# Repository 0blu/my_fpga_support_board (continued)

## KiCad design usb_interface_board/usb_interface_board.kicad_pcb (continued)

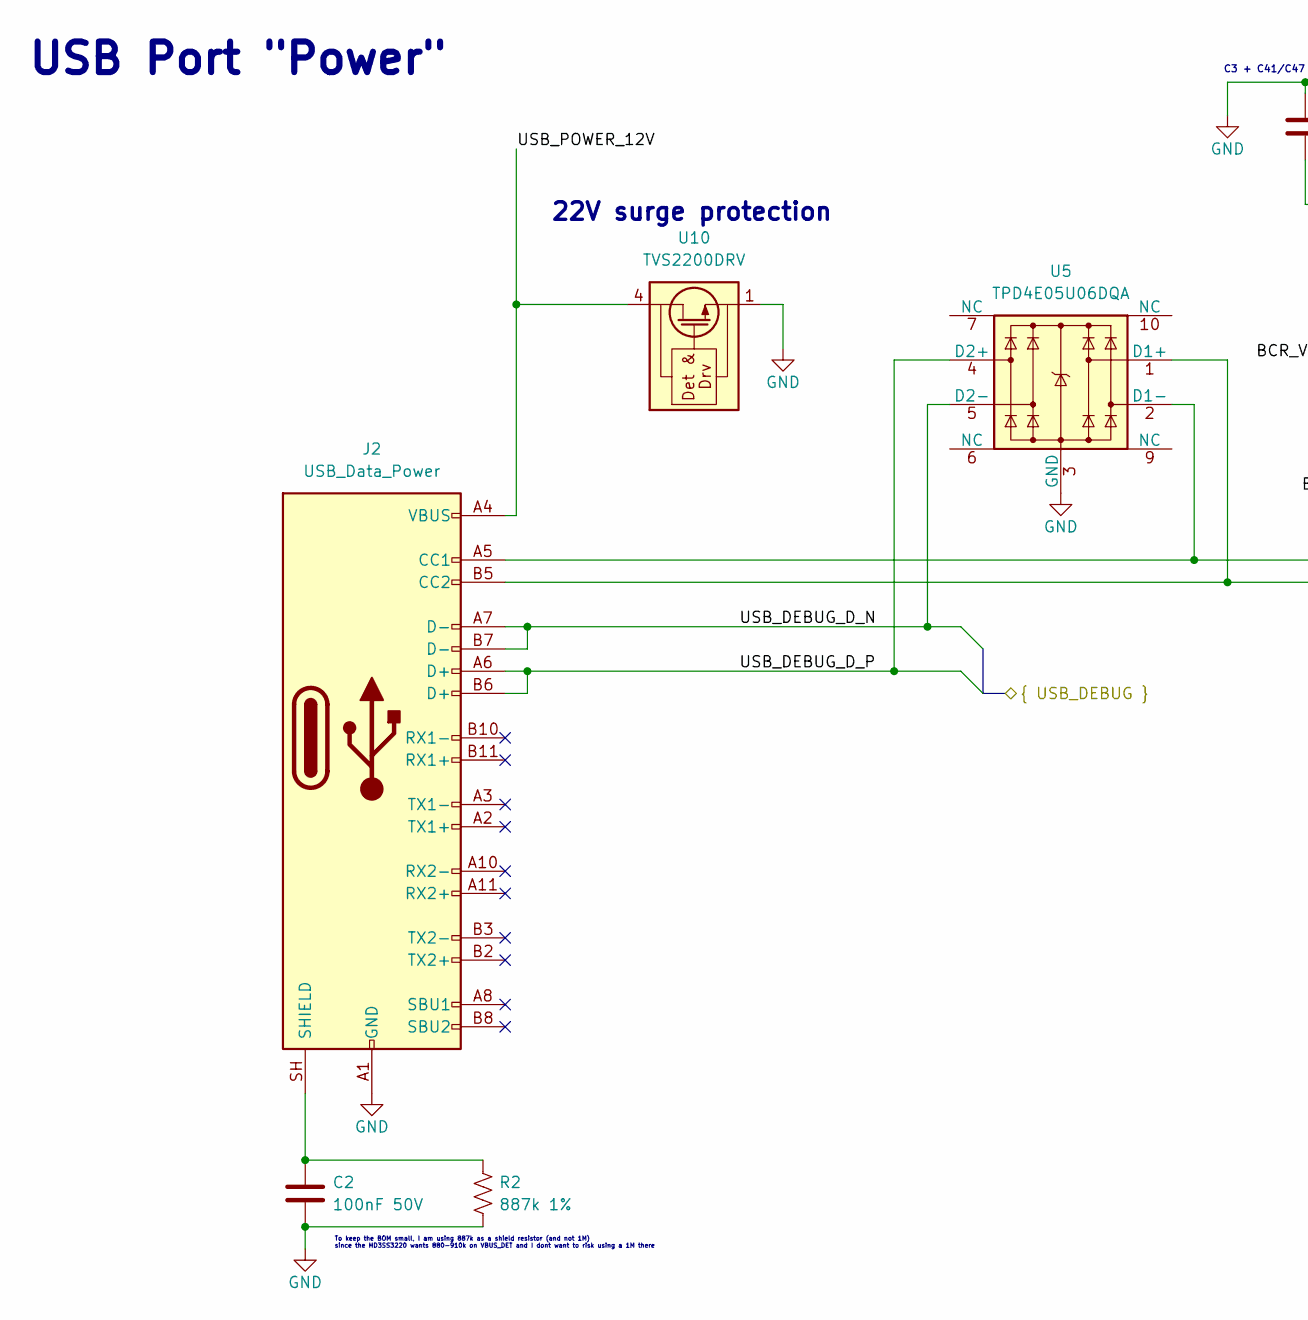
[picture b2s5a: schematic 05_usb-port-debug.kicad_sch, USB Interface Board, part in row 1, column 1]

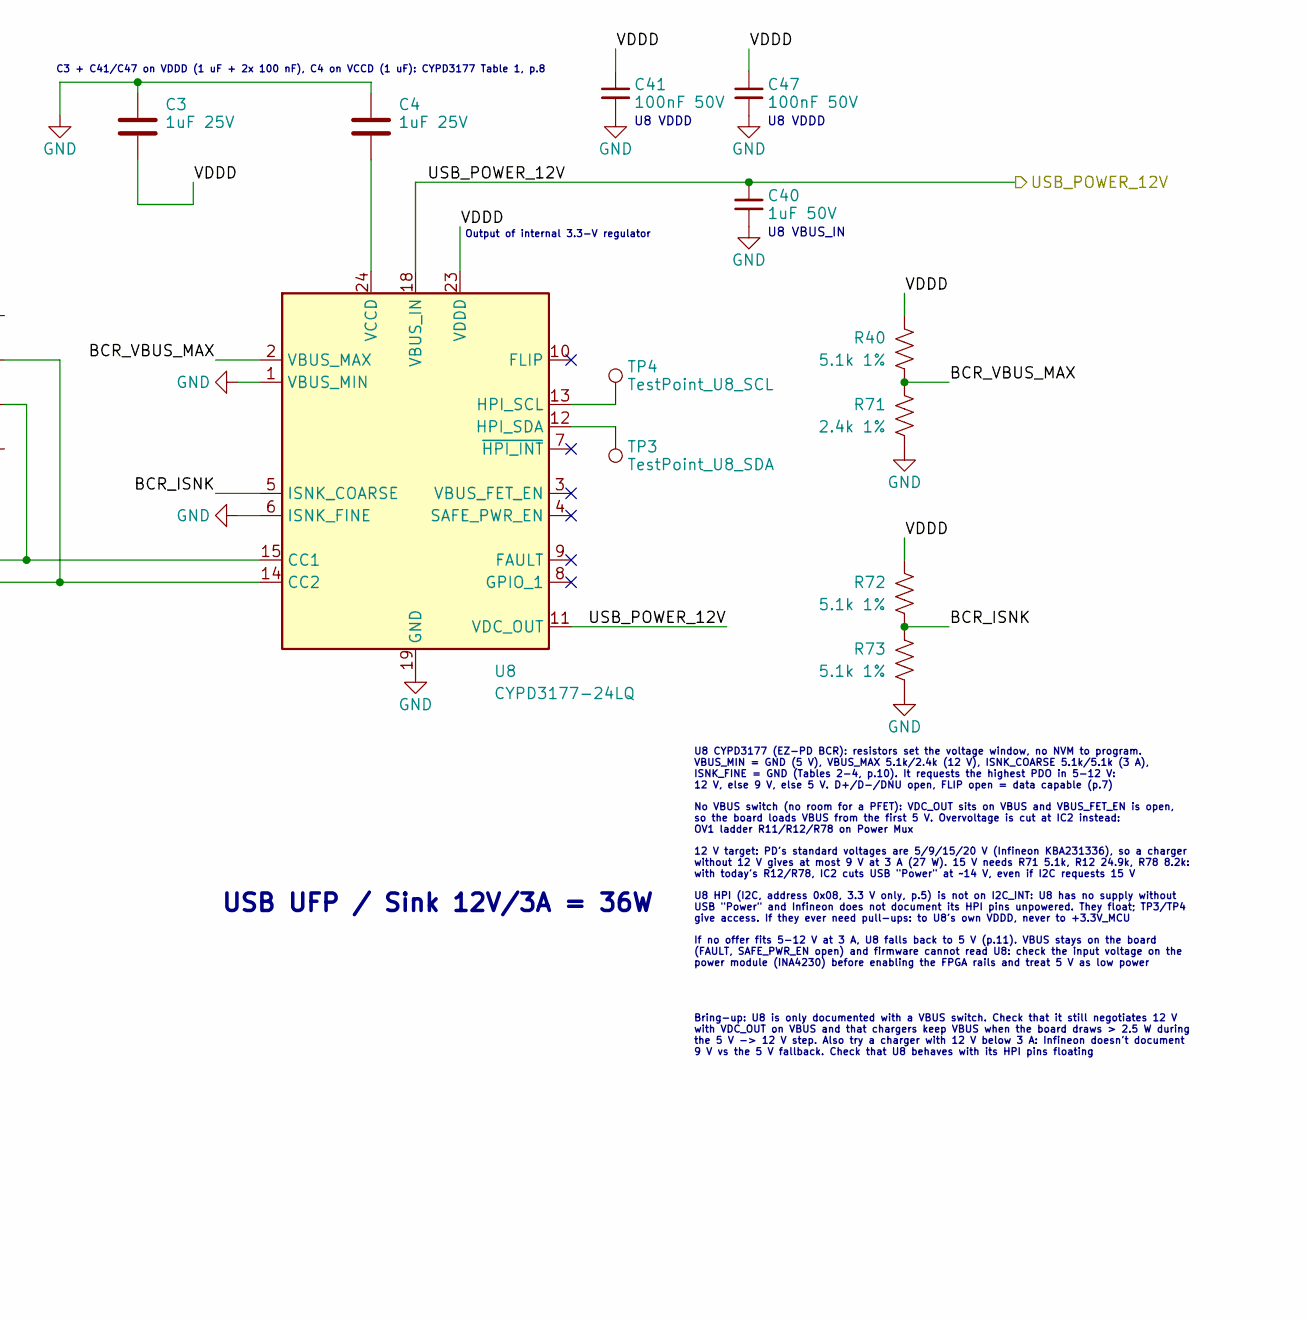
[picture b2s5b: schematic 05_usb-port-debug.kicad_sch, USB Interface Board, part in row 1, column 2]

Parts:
C2, C41, C47: 100nF 50V; C_0402_1005Metric; Manufacturer Part CL05B104KB54PNC; LCSC C307331
C3, C4: 1uF 25V; C_0402_1005Metric; Manufacturer Part CL05A105KA5NQNC; LCSC C52923
C40: 1uF 50V; C_0603_1608Metric; Manufacturer Part CL10A105KB8NNNC; LCSC C15849
J2: USB_Data_Power; USB_C_Receptacle_Molex_105450-0101; Manufacturer Part 105450-0101; LCSC C134092
R2: 887k 1%; R_0402_1005Metric; Manufacturer Part ERJ-2RKF8873X; LCSC C409935
R40, R72, R73: 5.1k 1%; R_0402_1005Metric; Manufacturer Part 0402WGF5101TCE; LCSC C25905
R71: 2.4k 1%; R_0402_1005Metric; Manufacturer Part RC0402FR-072K4L; LCSC C112296
TP3: TestPoint_U8_SDA; TestPoint_Pad_D1.0mm
TP4: TestPoint_U8_SCL; TestPoint_Pad_D1.0mm
U5: TPD4E05U06DQA; USON-10_2.5x1.0mm_P0.5mm; Manufacturer Part TPD4E05U06DQAR; LCSC C138714
U8: CYPD3177-24LQ; QFN-24-1EP_4x4mm_P0.5mm_EP2.75x2.75mm; Manufacturer Part CYPD3177-24LQXQT; LCSC C2952489
U10: TVS2200DRV; WSON-6-1EP_2x2mm_P0.65mm_EP1x1.6mm; Manufacturer Part TVS2200DRVR; LCSC C523793

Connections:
/EZ-USB 3.2 FX5/USB_DEBUG_D_N: J2.A7 (D-), J2.B7 (D-), U5.5 (D2-); also elsewhere on the board
/EZ-USB 3.2 FX5/USB_DEBUG_D_P: J2.A6 (D+), J2.B6 (D+), U5.4 (D2+); also elsewhere on the board
/USB Port "Power"/BCR_ISNK: R72.2, R73.1, U8.5 (ISNK_COARSE)
/USB Port "Power"/BCR_VBUS_MAX: R40.2, R71.1, U8.2 (VBUS_MAX)
/USB Port "Power"/USB_POWER_12V: C40.1, J2.A4 (VBUS), J2.A9 (VBUS), J2.B4 (VBUS), J2.B9 (VBUS), U8.11 (VDC_OUT), U8.18 (VBUS_IN), U10.4 (IN), U10.5 (IN), U10.6 (IN); also elsewhere on the board
/USB Port "Power"/VDDD: C3.2, C41.1, C47.1, R40.1, R72.1, U8.23 (VDDD)
GND: C2.2, C3.1, C4.1, C40.2, C41.2, C47.2, J2.A1 (GND), J2.A12 (GND), J2.B1 (GND), J2.B12 (GND), R2.2, R71.2, R73.2, U5.3 (GND), U5.8 (GND), U8.1 (VBUS_MIN), U8.6 (ISNK_FINE), U8.19 (GND), U8.22 (GND), U8.25 (GND), U10.1 (GND), U10.2 (GND), U10.3 (GND), U10.7 (GND); also elsewhere on the board
unnamed: J2.A5 (CC1), U5.2 (D1-), U8.15 (CC1)
unnamed: J2.B5 (CC2), U5.1 (D1+), U8.14 (CC2)
unnamed: C2.1, J2.SH (SHIELD), R2.1
unnamed: TP4.1 (1_1), U8.13 (HPI_SCL)
unnamed: TP3.1 (1_1), U8.12 (HPI_SDA)
unnamed: C4.2, U8.24 (VCCD)

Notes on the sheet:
U8 HPI (I2C, address 0x08, 3.3 V only, p.5) is not on I2C_INT: U8 has no supply without USB "Power" and Infineon does not document its HPI pins unpowered. They float; TP3/TP4 give access. If they ever need pull-ups: to U8's own VDDD, never to +3.3V_MCU
12 V target: PD's standard voltages are 5/9/15/20 V (Infineon KBA231336), so a charger without 12 V gives at most 9 V at 3 A (27 W). 15 V needs R71 5.1k, R12 24.9k, R78 8.2k: with today's R12/R78, IC2 cuts USB "Power" at ~14 V, even if I2C requests 15 V
Bring-up: U8 is only documented with a VBUS switch. Check that it still negotiates 12 V with VDC_OUT on VBUS and that chargers keep VBUS when the board draws > 2.5 W during the 5 V -> 12 V step. Also try a charger with 12 V below 3 A: Infineon doesn't document 9 V vs the 5 V fallback. Check that U8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
U8 VDDD
U8 VBUS_IN
To keep the BOM small, I am using 887k as a shield resistor (and not 1M) since the HD3SS3220 wants 880-910k on VBUS_DET and I dont want to risk using a 1M there
Output of internal 3.3-V regulator
USB Port "Power"
No VBUS switch (no room for a PFET): VDC_OUT sits on VBUS and VBUS_FET_EN is open, so the board loads VBUS from the first 5 V. Overvoltage is cut at IC2 instead: OV1 ladder R11/R12/R78 on Power Mux
U8 CYPD3177 (EZ-PD BCR): resistors set the voltage window, no NVM to program. VBUS_MIN = GND (5 V), VBUS_MAX 5.1k/2.4k (12 V), ISNK_COARSE 5.1k/5.1k (3 A), ISNK_FINE = GND (Tables 2-4, p.10). It requests the highest PDO in 5-12 V: 12 V, else 9 V, else 5 V. D+/D-/DNU open, FLIP open = data capable (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
22V surge protection
C3 + C41/C47 on VDDD (1 uF + 2x 100 nF), C4 on VCCD (1 uF): CYPD3177 Table 1, p.8
USB UFP / Sink 12V/3A = 36W
If no offer fits 5-12 V at 3 A, U8 falls back to 5 V (p.11). VBUS stays on the board (FAULT, SAFE_PWR_EN open) and firmware cannot read U8: check the input voltage on the power module (INA4230) before enabling the FPGA rails and treat 5 V as low power

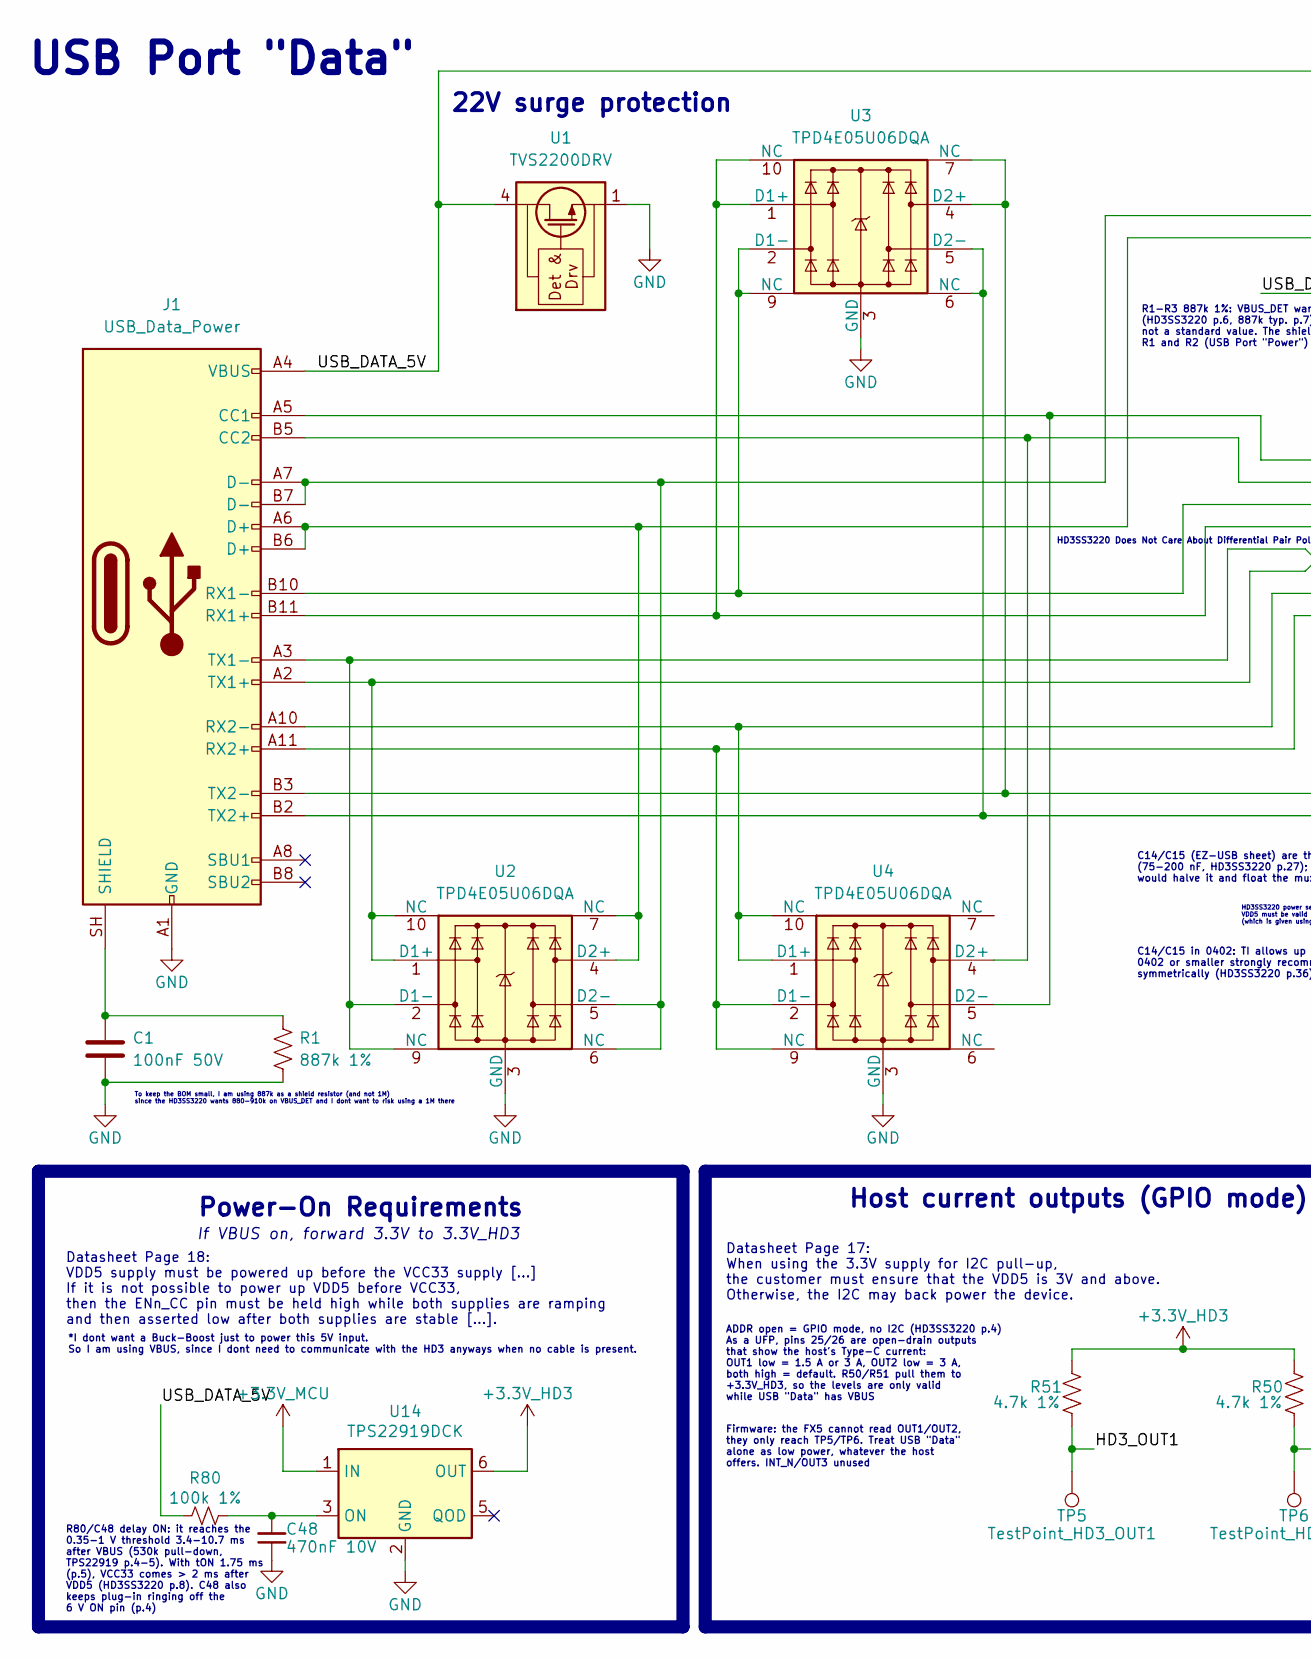
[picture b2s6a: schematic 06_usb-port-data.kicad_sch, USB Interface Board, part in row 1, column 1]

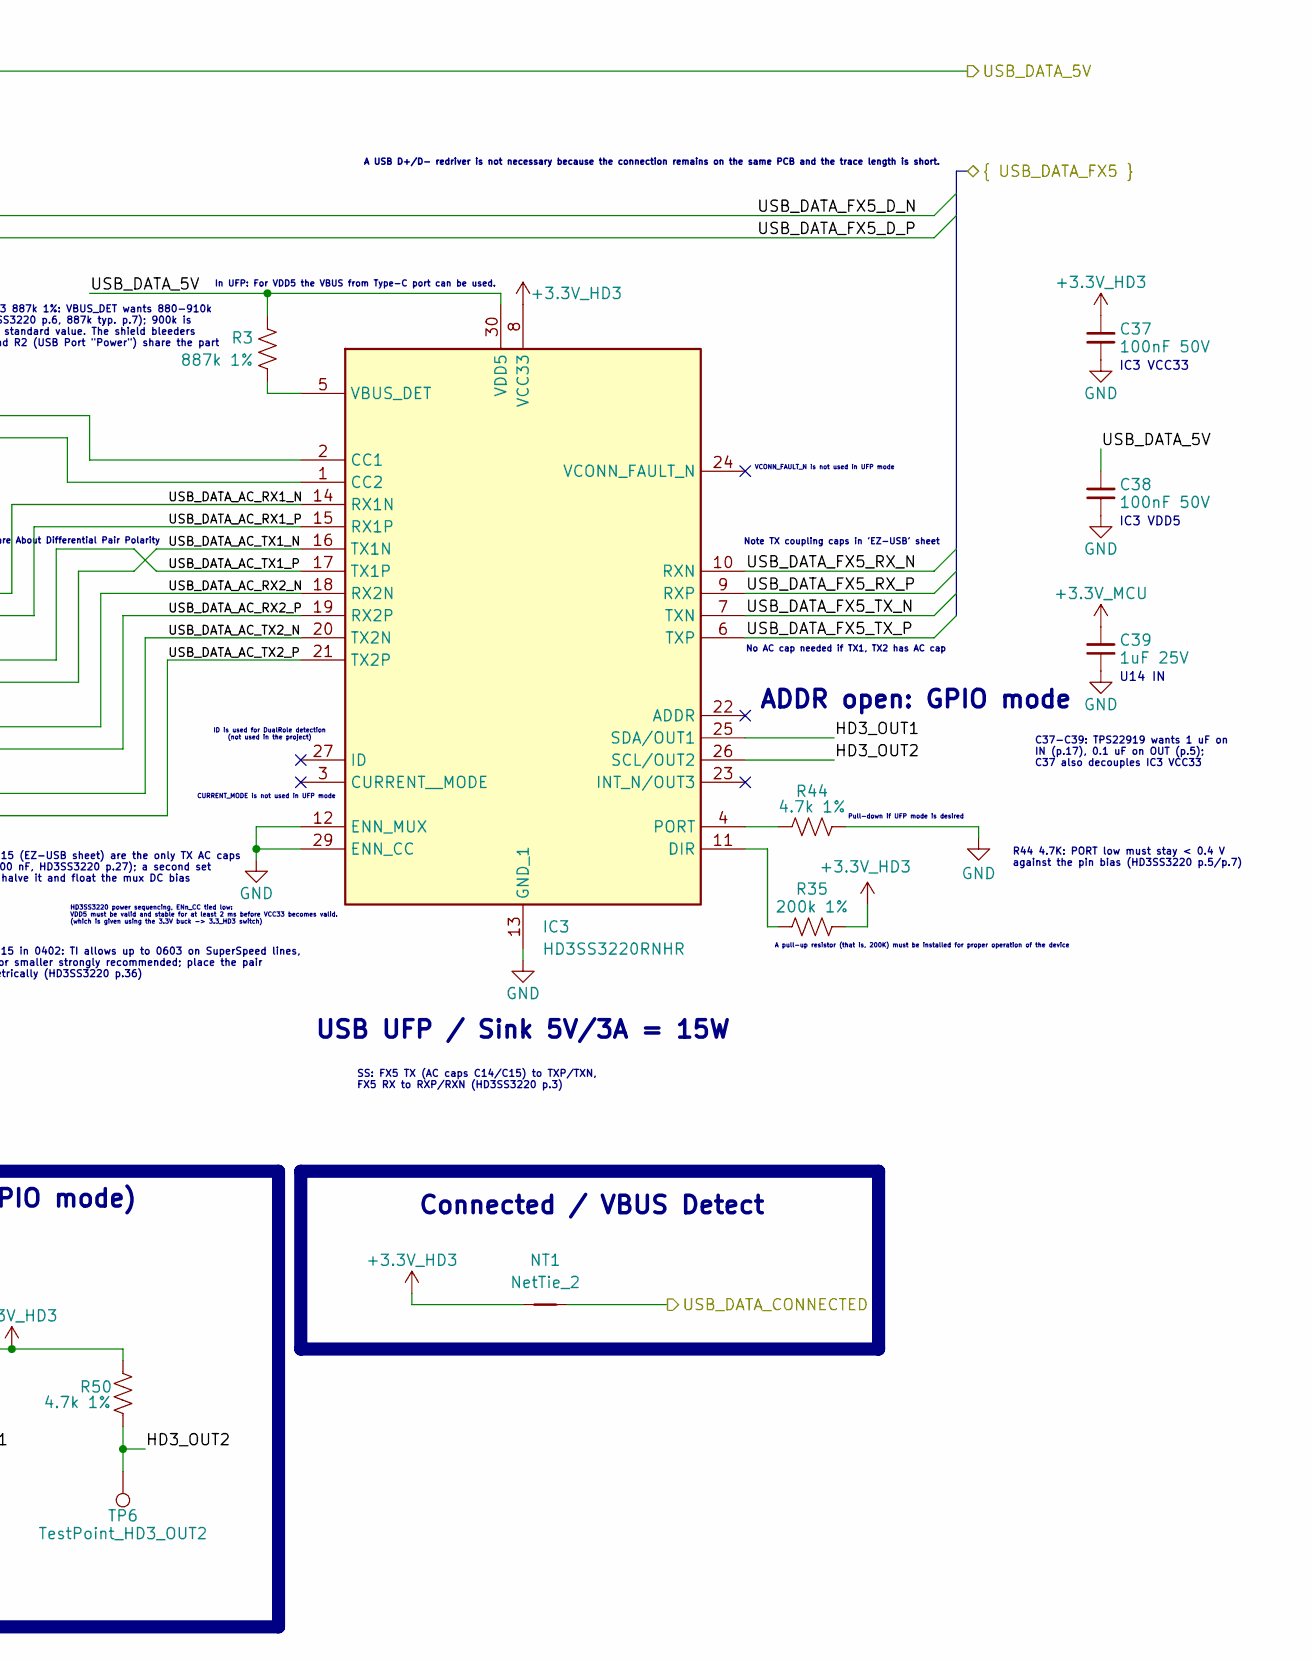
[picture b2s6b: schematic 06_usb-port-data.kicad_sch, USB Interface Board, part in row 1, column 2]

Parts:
C1, C37, C38: 100nF 50V; C_0402_1005Metric; Manufacturer Part CL05B104KB54PNC; LCSC C307331
C39: 1uF 25V; C_0402_1005Metric; Manufacturer Part CL05A105KA5NQNC; LCSC C52923
C48: 470nF 10V; C_0402_1005Metric; Manufacturer Part CL05A474KP5NNNC; LCSC C47339
IC3: HD3SS3220RNHR; QFN40P250X450X80-31N-D; Mouser Part Number 595-HD3SS3220RNHR
J1: USB_Data_Power; USB_C_Receptacle_Molex_105450-0101; Manufacturer Part 105450-0101; LCSC C134092
NT1: NetTie_2; NetTie-2_SMD_Pad0.15mm
R1, R3: 887k 1%; R_0402_1005Metric; Manufacturer Part ERJ-2RKF8873X; LCSC C409935
R35: 200k 1%; R_0402_1005Metric; Manufacturer Part 0402WGF2003TCE; LCSC C25764
R44, R50, R51: 4.7k 1%; R_0402_1005Metric; Manufacturer Part 0402WGF4701TCE; LCSC C25900
R80: 100k 1%; R_0402_1005Metric; Manufacturer Part 0402WGF1003TCE; LCSC C25741
TP5: TestPoint_HD3_OUT1; TestPoint_Pad_D1.0mm
TP6: TestPoint_HD3_OUT2; TestPoint_Pad_D1.0mm
U1: TVS2200DRV; WSON-6-1EP_2x2mm_P0.65mm_EP1x1.6mm; Manufacturer Part TVS2200DRVR; LCSC C523793
U2, U3, U4: TPD4E05U06DQA; USON-10_2.5x1.0mm_P0.5mm; Manufacturer Part TPD4E05U06DQAR; LCSC C138714
U14: TPS22919DCK; SOT-363_SC-70-6; Manufacturer Part TPS22919DCKR; LCSC C2149796

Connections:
+3.3V_HD3: C37.1, IC3.8 (VCC33), NT1.1, R35.2, R50.1, R51.1, U14.6 (OUT)
+3.3V_MCU: C39.1, U14.1 (IN); also elsewhere on the board
/EZ-USB 3.2 FX5/USB_DATA_5V: C38.1, IC3.30 (VDD5), J1.A4 (VBUS), J1.A9 (VBUS), J1.B4 (VBUS), J1.B9 (VBUS), R3.2, R80.1, U1.4 (IN), U1.5 (IN), U1.6 (IN); also elsewhere on the board
/EZ-USB 3.2 FX5/USB_DATA_CONNECTED: NT1.2; also elsewhere on the board
/EZ-USB 3.2 FX5/USB_DATA_FX5_D_N: J1.A7 (D-), J1.B7 (D-), U2.5 (D2-), U2.6 (NC); also elsewhere on the board
/EZ-USB 3.2 FX5/USB_DATA_FX5_D_P: J1.A6 (D+), J1.B6 (D+), U2.4 (D2+), U2.7 (NC); also elsewhere on the board
/EZ-USB 3.2 FX5/USB_DATA_FX5_RX_N: IC3.10 (RXN); also elsewhere on the board
/EZ-USB 3.2 FX5/USB_DATA_FX5_RX_P: IC3.9 (RXP); also elsewhere on the board
/EZ-USB 3.2 FX5/USB_DATA_FX5_TX_N: IC3.7 (TXN); also elsewhere on the board
/EZ-USB 3.2 FX5/USB_DATA_FX5_TX_P: IC3.6 (TXP); also elsewhere on the board
/USB Port "Data"/HD3_OUT1: IC3.25 (SDA/OUT1), R51.2, TP5.1 (1_1)
/USB Port "Data"/HD3_OUT2: IC3.26 (SCL/OUT2), R50.2, TP6.1 (1_1)
/USB Port "Data"/USB_DATA_AC_RX1_N: IC3.14 (RX1N), J1.B10 (RX1-), U3.2 (D1-), U3.9 (NC)
/USB Port "Data"/USB_DATA_AC_RX1_P: IC3.15 (RX1P), J1.B11 (RX1+), U3.1 (D1+), U3.10 (NC)
/USB Port "Data"/USB_DATA_AC_RX2_N: IC3.18 (RX2N), J1.A10 (RX2-), U4.1 (D1+), U4.10 (NC)
/USB Port "Data"/USB_DATA_AC_RX2_P: IC3.19 (RX2P), J1.A11 (RX2+), U4.2 (D1-), U4.9 (NC)
/USB Port "Data"/USB_DATA_AC_TX1_N: IC3.16 (TX1N), J1.A2 (TX1+), U2.1 (D1+), U2.10 (NC)
/USB Port "Data"/USB_DATA_AC_TX1_P: IC3.17 (TX1P), J1.A3 (TX1-), U2.2 (D1-), U2.9 (NC)
/USB Port "Data"/USB_DATA_AC_TX2_N: IC3.20 (TX2N), J1.B3 (TX2-), U3.4 (D2+), U3.7 (NC)
/USB Port "Data"/USB_DATA_AC_TX2_P: IC3.21 (TX2P), J1.B2 (TX2+), U3.5 (D2-), U3.6 (NC)
GND: C1.2, C37.2, C38.2, C39.2, C48.2, IC3.12 (ENN_MUX), IC3.13 (GND_1), IC3.28 (GND_2), IC3.29 (ENN_CC), IC3.31 (EP), J1.A1 (GND), J1.A12 (GND), J1.B1 (GND), J1.B12 (GND), R1.2, R44.2, U1.1 (GND), U1.2 (GND), U1.3 (GND), U1.7 (GND), U2.3 (GND), U2.8 (GND), U3.3 (GND), U3.8 (GND), U4.3 (GND), U4.8 (GND), U14.2 (GND); also elsewhere on the board
unnamed: IC3.2 (CC1), J1.A5 (CC1), U4.5 (D2-)
unnamed: IC3.1 (CC2), J1.B5 (CC2), U4.4 (D2+)
unnamed: IC3.11 (DIR), R35.1
unnamed: IC3.4 (PORT), R44.1
unnamed: IC3.5 (VBUS_DET), R3.1
unnamed: C1.1, J1.SH (SHIELD), R1.1
unnamed: C48.1, R80.2, U14.3 (ON)

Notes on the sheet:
CURRENT_MODE is not used in UFP mode
Connected / VBUS Detect
R1-R3 887k 1%: VBUS_DET wants 880-910k (HD3SS3220 p.6, 887k typ. p.7); 900k is not a standard value. The shield bleeders R1 and R2 (USB Port "Power") share the part
ID is used for DualRole detection (not used in the project)
Power-On Requirements
Note TX coupling caps in 'EZ-USB' sheet
A pull-up resistor (that is, 200K) must be installed for proper operation of the device
USB Port "Data"
HD3SS3220 Does Not Care About Differential Pair Polarity
USB UFP / Sink 5V/3A = 15W
A USB D+/D− redriver is not necessary because the connection remains on the same PCB and the trace length is short.
Firmware: the FX5 cannot read OUT1/OUT2, they only reach TP5/TP6. Treat USB "Data" alone as low power, whatever the host offers. INT_N/OUT3 unused
HD3SS3220 power sequencing, ENn_CC tied low: VDD5 must be valid and stable for at least 2 ms before VCC33 becomes valid. (which is given using the 3.3V buck -> 3.3_HD3 switch)
R80/C48 delay ON: it reaches the 0.35-1 V threshold 3.4-10.7 ms after VBUS (530k pull-down, TPS22919 p.4-5). With tON 1.75 ms (p.5), VCC33 comes > 2 ms after VDD5 (HD3SS3220 p.8). C48 also keeps plug-in ringing off the 6 V ON pin (p.4)
If VBUS on, forward 3.3V to 3.3V_HD3
VCONN_FAULT_N is not used in UFP mode
Datasheet Page 17: When using the 3.3V supply for I2C pull-up, the customer must ensure that the VDD5 is 3V and above. Otherwise, the I2C may back power the device.
*I dont want a Buck-Boost just to power this 5V input. So I am using VBUS, since I dont need to communicate with the HD3 anyways when no cable is present.
SS: FX5 TX (AC caps C14/C15) to TXP/TXN, FX5 RX to RXP/RXN (HD3SS3220 p.3)
R44 4.7K: PORT low must stay < 0.4 V against the pin bias (HD3SS3220 p.5/p.7)
C14/C15 (EZ-USB sheet) are the only TX AC caps (75-200 nF, HD3SS3220 p.27); a second set would halve it and float the mux DC bias
IC3 VDD5
No AC cap needed if TX1, TX2 has AC cap
IC3 VCC33
Datasheet Page 18: VDD5 supply must be powered up before the VCC33 supply [...] If it is not possible to power up VDD5 before VCC33, then the ENn_CC pin must be held high while both supplies are ramping and then asserted low after both supplies are stable [...].
Host current outputs (GPIO mode)
U14 IN
C37-C39: TPS22919 wants 1 uF on IN (p.17), 0.1 uF on OUT (p.5); C37 also decouples IC3 VCC33
In UFP: For VDD5 the VBUS from Type-C port can be used.
C14/C15 in 0402: TI allows up to 0603 on SuperSpeed lines, 0402 or smaller strongly recommended; place the pair symmetrically (HD3SS3220 p.36)
To keep the BOM small, I am using 887k as a shield resistor (and not 1M) since the HD3SS3220 wants 880-910k on VBUS_DET and I dont want to risk using a 1M there
22V surge protection
ADDR open: GPIO mode
Pull-down if UFP mode is desired
ADDR open = GPIO mode, no I2C (HD3SS3220 p.4) As a UFP, pins 25/26 are open-drain outputs that show the host's Type-C current: OUT1 low = 1.5 A or 3 A, OUT2 low = 3 A, both high = default. R50/R51 pull them to +3.3V_HD3, so the levels are only valid while USB "Data" has VBUS

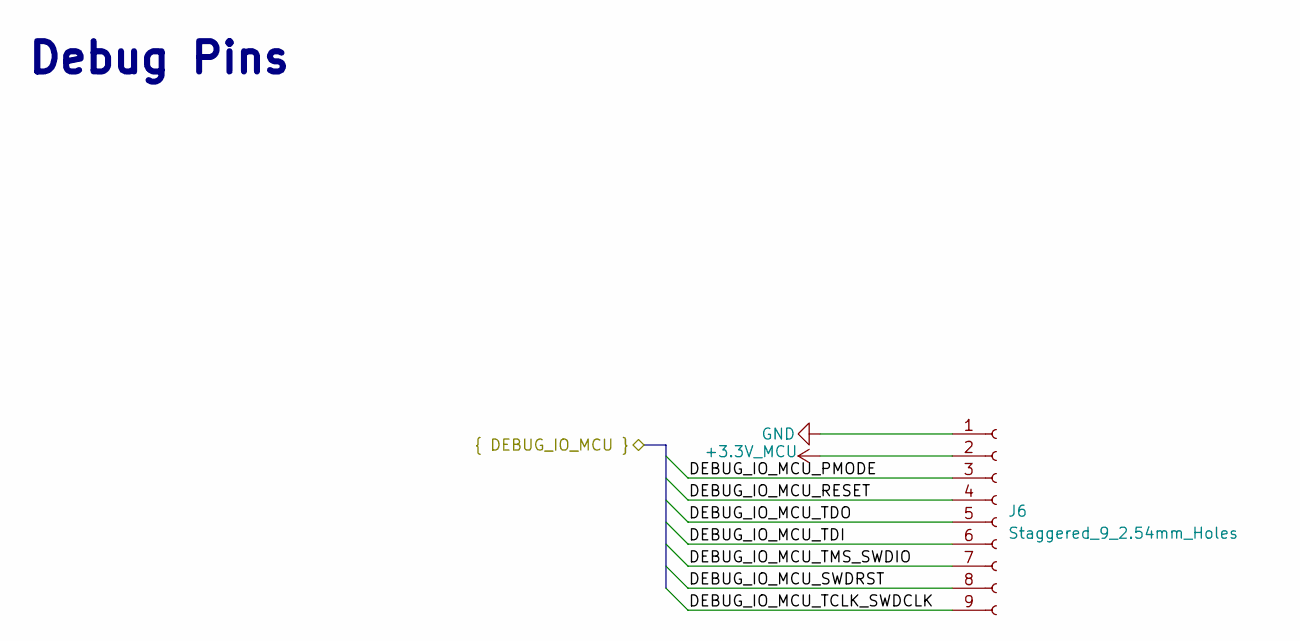
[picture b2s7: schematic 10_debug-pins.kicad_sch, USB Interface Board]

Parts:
J6: Staggered_9_2.54mm_Holes; 09_Staggered_GPIO_holes

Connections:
+3.3V_MCU: J6.2; also elsewhere on the board
/Debug Pins/DEBUG_IO_MCU_PMODE: J6.3; also elsewhere on the board
/Debug Pins/DEBUG_IO_MCU_RESET: J6.4; also elsewhere on the board
/Debug Pins/DEBUG_IO_MCU_SWDRST: J6.8; also elsewhere on the board
/Debug Pins/DEBUG_IO_MCU_TCLK_SWDCLK: J6.9; also elsewhere on the board
/Debug Pins/DEBUG_IO_MCU_TDI: J6.6; also elsewhere on the board
/Debug Pins/DEBUG_IO_MCU_TDO: J6.5; also elsewhere on the board
/Debug Pins/DEBUG_IO_MCU_TMS_SWDIO: J6.7; also elsewhere on the board
GND: J6.1; also elsewhere on the board

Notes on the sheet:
Debug Pins

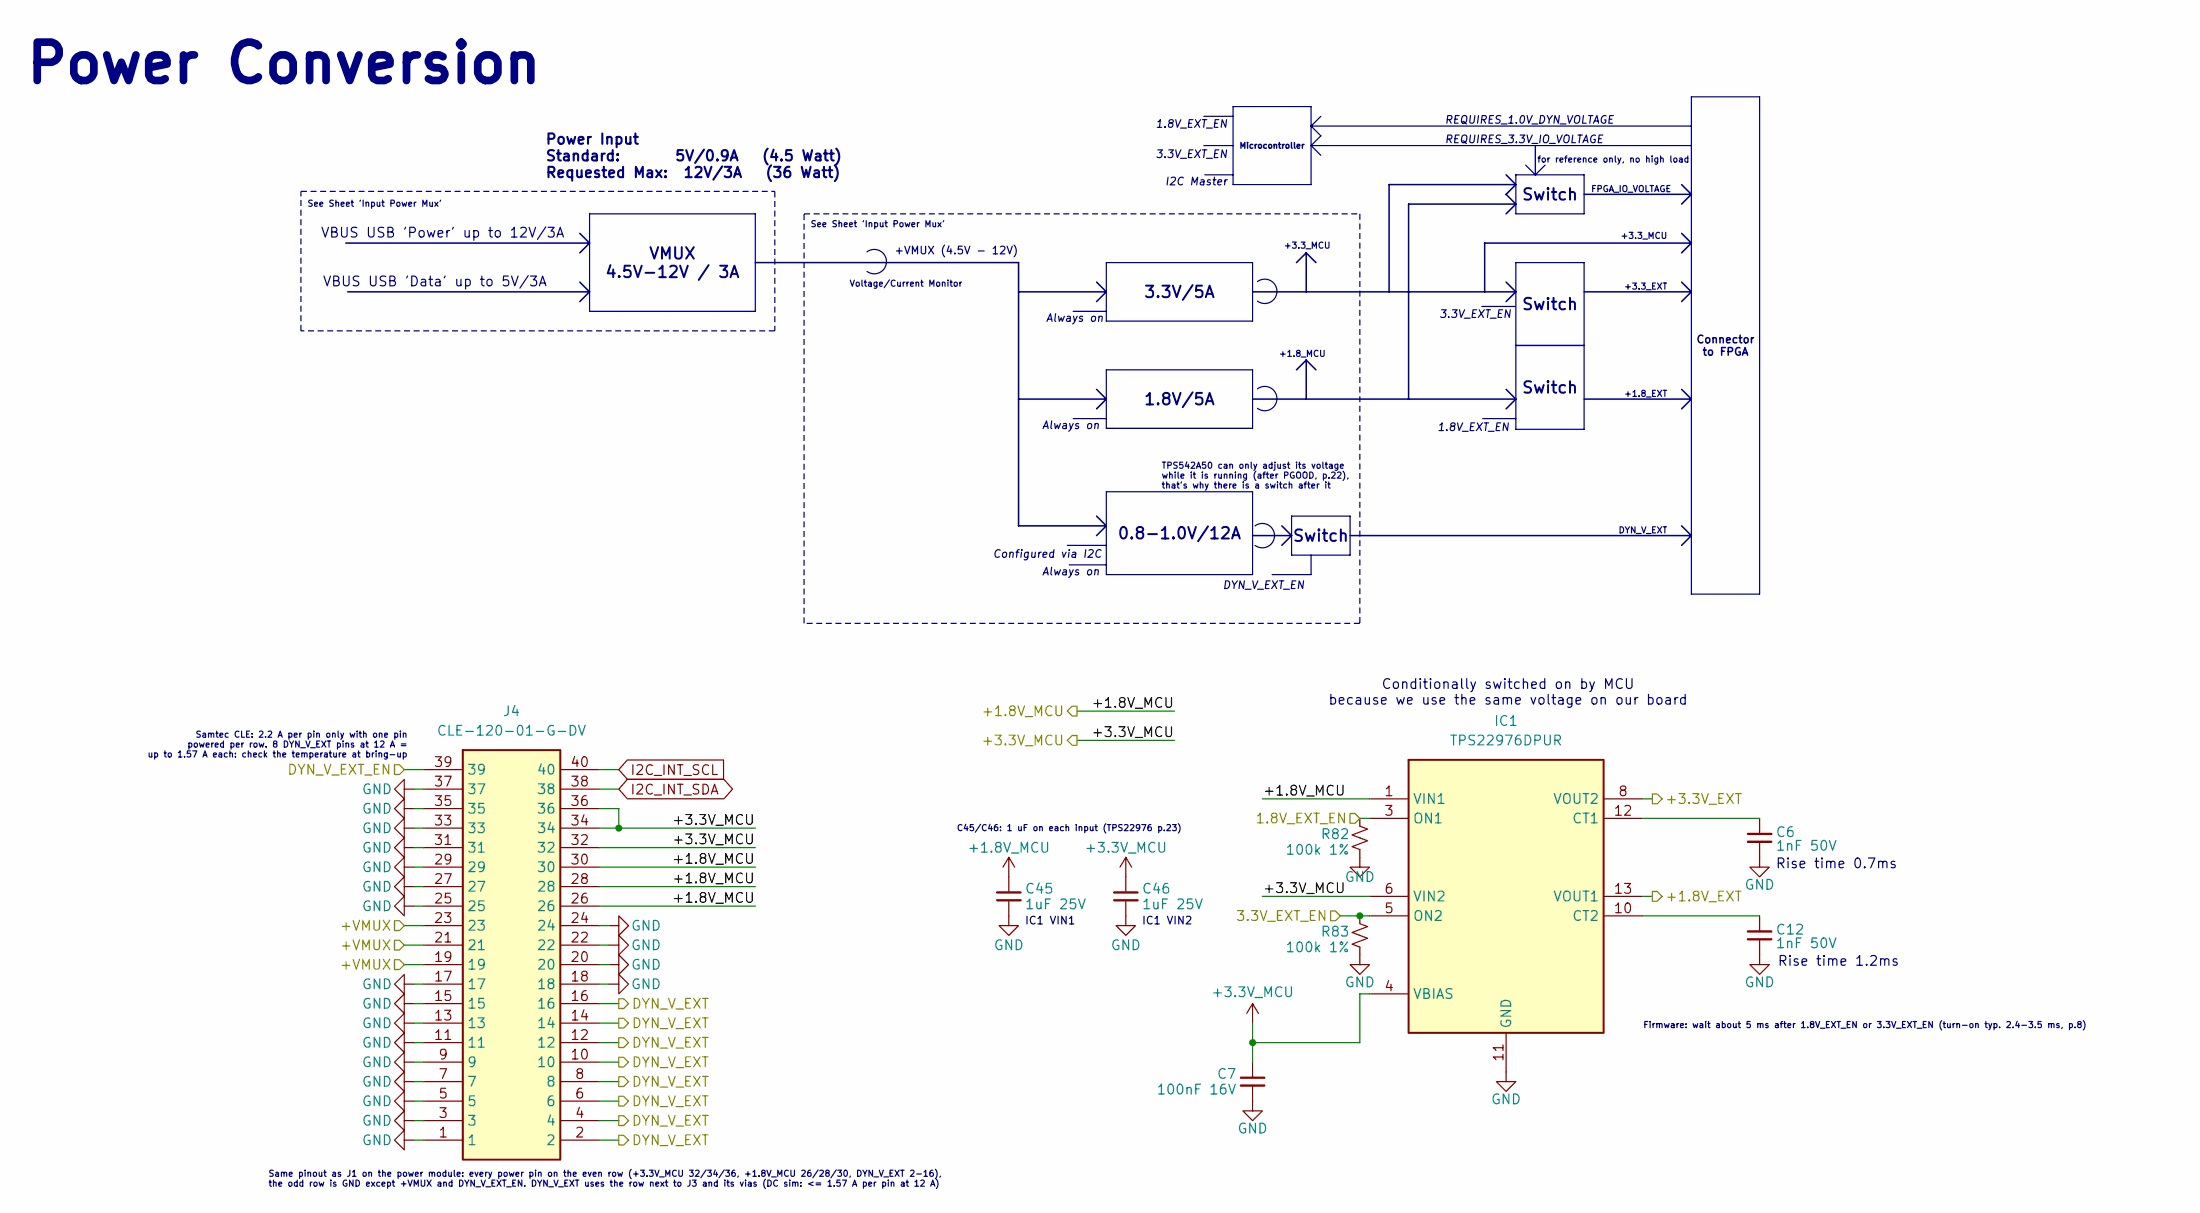
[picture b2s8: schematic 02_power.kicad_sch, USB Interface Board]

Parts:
C6, C12: 1nF 50V; C_0402_1005Metric; Manufacturer Part 0402B102K500NT; LCSC C1523
C7: 100nF 16V; C_0201_0603Metric; Manufacturer Part CL03A104KO3NNNC; LCSC C307380
C45, C46: 1uF 25V; C_0402_1005Metric; Manufacturer Part CL05A105KA5NQNC; LCSC C52923
IC1: TPS22976DPUR; TPS22976ADPUR; Mouser Part Number 595-TPS22976DPUR
J4: CLE-120-01-G-DV; Manufacturer Part CLE-120-01-G-DV-K-TR; LCSC C6484368
R82, R83: 100k 1%; R_0402_1005Metric; Manufacturer Part 0402WGF1003TCE; LCSC C25741

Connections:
+1.8V_MCU: C45.1, IC1.1 (VIN1), IC1.2 (VIN1_2), J4.26, J4.28, J4.30; also elsewhere on the board
+3.3V_MCU: C7.1, C46.1, IC1.4 (VBIAS), IC1.6 (VIN2), IC1.7 (VIN2_2), J4.32, J4.34, J4.36; also elsewhere on the board
/EZ-USB 3.2 FX5/1.8V_EXT_EN: IC1.3 (ON1), R82.1; also elsewhere on the board
/EZ-USB 3.2 FX5/3.3V_EXT_EN: IC1.5 (ON2), R83.1; also elsewhere on the board
/EZ-USB 3.2 FX5/DYN_V_EXT_EN: J4.39; also elsewhere on the board
/FPGA Board Connector/+1.8V_EXT: IC1.13 (VOUT1), IC1.14 (VOUT1_2); also elsewhere on the board
/FPGA Board Connector/+3.3V_EXT: IC1.8 (VOUT2), IC1.9 (VOUT2_2); also elsewhere on the board
/FPGA Board Connector/DYN_V_EXT: J4.2, J4.4, J4.6, J4.8, J4.10, J4.12, J4.14, J4.16; also elsewhere on the board
/Power Board Connector/+VMUX: J4.19, J4.21, J4.23; also elsewhere on the board
GND: C6.2, C7.2, C12.2, C45.2, C46.2, IC1.11 (GND), IC1.15 (GND_2), J4.1, J4.3, J4.5, J4.7, J4.9, J4.11, J4.13, J4.15, J4.17, J4.18, J4.20, J4.22, J4.24, J4.25, J4.27, J4.29, J4.31, J4.33, J4.35, J4.37, R82.2, R83.2; also elsewhere on the board
I2C_INT_SCL: J4.40; also elsewhere on the board
I2C_INT_SDA: J4.38; also elsewhere on the board
unnamed: C6.1, IC1.12 (CT1)
unnamed: C12.1, IC1.10 (CT2)

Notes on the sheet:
TPS542A50 can only adjust its voltage while it is running (after PGOOD, p.22), that's why there is a switch after it
+1.8_EXT
See Sheet 'Input Power Mux'
+3.3_MCU
Configured via I2C
DYN_V_EXT_EN
for reference only, no high load
REQUIRES_3.3V_IO_VOLTAGE
+3.3_EXT
Same pinout as J1 on the power module: every power pin on the even row (+3.3V_MCU 32/34/36, +1.8V_MCU 26/28/30, DYN_V_EXT 2-16), the odd row is GND except +VMUX and DYN_V_EXT_EN. DYN_V_EXT uses the row next to J3 and its vias (DC sim: <= 1.57 A per pin at 12 A)
IC1 VIN2
FPGA_IO_VOLTAGE
VBUS USB 'Data' up to 5V/3A
1.8V_EXT_EN
Always on
IC1 VIN1
Samtec CLE: 2.2 A per pin only with one pin powered per row. 8 DYN_V_EXT pins at 12 A = up to 1.57 A each: check the temperature at bring-up
Firmware: wait about 5 ms after 1.8V_EXT_EN or 3.3V_EXT_EN (turn-on typ. 2.4-3.5 ms, p.8)
Conditionally switched on by MCU because we use the same voltage on our board
Voltage/Current Monitor
VBUS USB 'Power' up to 12V/3A
+1.8_MCU
REQUIRES_1.0V_DYN_VOLTAGE
3.3V_EXT_EN
Rise time 1.2ms
Power Input Standard: 5V/0.9A (4.5 Watt) Requested Max: 12V/3A (36 Watt)
+VMUX (4.5V - 12V)
I2C Master
C45/C46: 1 uF on each input (TPS22976 p.23)
Power Conversion
DYN_V_EXT
Rise time 0.7ms
Switch
Connector to FPGA
0.8-1.0V/12A
1.8V/5A
VMUX 4.5V-12V / 3A
Microcontroller
3.3V/5A

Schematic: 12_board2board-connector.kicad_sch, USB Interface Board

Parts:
J3: QSH-030-01-L-D; QSH03001LDK; Manufacturer Part QSH-030-01-L-D-K-TR; LCSC C3653140

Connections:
+3.3V_MCU: J3.53; also elsewhere on the board
/100MHz Oscillator/CLK_100MHZ: J3.31; also elsewhere on the board
/EZ-USB 3.2 FX5/FIFO_A0: J3.48; also elsewhere on the board
/EZ-USB 3.2 FX5/FIFO_A1: J3.6; also elsewhere on the board
/EZ-USB 3.2 FX5/FIFO_CLK: J3.44; also elsewhere on the board
/EZ-USB 3.2 FX5/FIFO_D0: J3.2; also elsewhere on the board
/EZ-USB 3.2 FX5/FIFO_D1: J3.8; also elsewhere on the board
/EZ-USB 3.2 FX5/FIFO_D2: J3.16; also elsewhere on the board
/EZ-USB 3.2 FX5/FIFO_D3: J3.22; also elsewhere on the board
/EZ-USB 3.2 FX5/FIFO_D4: J3.30; also elsewhere on the board
/EZ-USB 3.2 FX5/FIFO_D5: J3.36; also elsewhere on the board
/EZ-USB 3.2 FX5/FIFO_D6: J3.40; also elsewhere on the board
/EZ-USB 3.2 FX5/FIFO_D7: J3.46; also elsewhere on the board
/EZ-USB 3.2 FX5/FIFO_D8: J3.4; also elsewhere on the board
/EZ-USB 3.2 FX5/FIFO_D9: J3.24; also elsewhere on the board
/EZ-USB 3.2 FX5/FIFO_D10: J3.12; also elsewhere on the board
/EZ-USB 3.2 FX5/FIFO_D11: J3.20; also elsewhere on the board
/EZ-USB 3.2 FX5/FIFO_D12: J3.32; also elsewhere on the board
/EZ-USB 3.2 FX5/FIFO_D13: J3.34; also elsewhere on the board
/EZ-USB 3.2 FX5/FIFO_D14: J3.38; also elsewhere on the board
/EZ-USB 3.2 FX5/FIFO_D15: J3.42; also elsewhere on the board
/EZ-USB 3.2 FX5/GPIO_B2B_0: J3.1; also elsewhere on the board
/EZ-USB 3.2 FX5/GPIO_B2B_1: J3.3; also elsewhere on the board
/EZ-USB 3.2 FX5/GPIO_B2B_2: J3.5; also elsewhere on the board
/EZ-USB 3.2 FX5/GPIO_B2B_3: J3.7; also elsewhere on the board
/EZ-USB 3.2 FX5/GPIO_B2B_3V3_0: J3.58; also elsewhere on the board
/EZ-USB 3.2 FX5/GPIO_B2B_3V3_1: J3.60; also elsewhere on the board
/EZ-USB 3.2 FX5/JTAG_FPGA_TCK: J3.54; also elsewhere on the board
/EZ-USB 3.2 FX5/JTAG_FPGA_TDI: J3.56; also elsewhere on the board
/EZ-USB 3.2 FX5/JTAG_FPGA_TDO: J3.52; also elsewhere on the board
/EZ-USB 3.2 FX5/JTAG_FPGA_TMS: J3.50; also elsewhere on the board
/EZ-USB 3.2 FX5/REQUIRES_1.0V_DYN_VOLTAGE: J3.55; also elsewhere on the board
/EZ-USB 3.2 FX5/REQUIRES_3.3V_IO_VOLTAGE: J3.57; also elsewhere on the board
/EZ-USB 3.2 FX5/~FIFO_FULL: J3.28; also elsewhere on the board
/EZ-USB 3.2 FX5/~FIFO_OE: J3.14; also elsewhere on the board
/EZ-USB 3.2 FX5/~FIFO_PKTEND: J3.26; also elsewhere on the board
/EZ-USB 3.2 FX5/~FIFO_RD: J3.18; also elsewhere on the board
/EZ-USB 3.2 FX5/~FIFO_WR: J3.10; also elsewhere on the board
/FPGA Board Connector/+1.8V_EXT: J3.33, J3.35, J3.37, J3.39, J3.41; also elsewhere on the board
/FPGA Board Connector/+3.3V_EXT: J3.43, J3.45, J3.47, J3.49, J3.51; also elsewhere on the board
/FPGA Board Connector/DYN_V_EXT: J3.11, J3.13, J3.15, J3.17, J3.19, J3.21, J3.23, J3.25, J3.27, J3.29; also elsewhere on the board
FPGA_IO_VOLTAGE: J3.59; also elsewhere on the board
GND: J3.MP1, J3.MP2, J3.MP3, J3.MP4; also elsewhere on the board

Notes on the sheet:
Pull to +3.3V_MCU or GND to set the input
low = 1.8V, high = 3.3V
FPGA Board Connector
8 Amp
Each pin can carry up to 2A
low = 0.85V, high = 1.0V
Additional power pins used to lower path resistance and minimize voltage drop
12 Amp
Samtec QSH: 2 A per pin only with one pin powered per row. 10 DYN_V_EXT pins at 12 A = 1.2 A each: check the temperature at bring-up

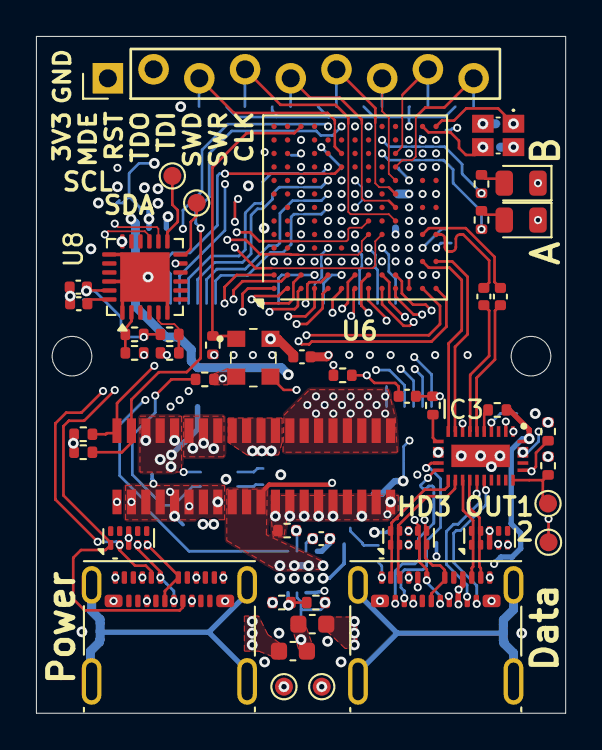
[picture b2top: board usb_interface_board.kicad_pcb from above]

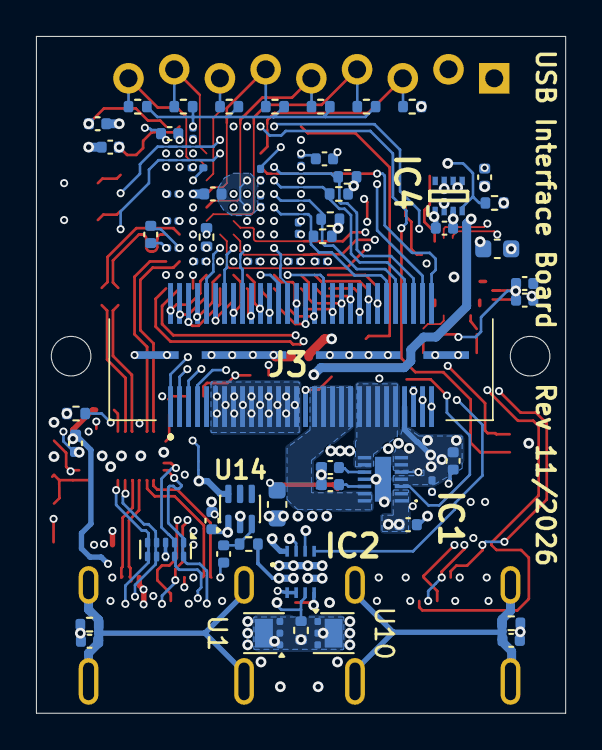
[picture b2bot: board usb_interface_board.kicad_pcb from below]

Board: 6 copper layers, 29.4 x 37.6 mm, 111 parts (62 on the bottom side), 113 nets.
